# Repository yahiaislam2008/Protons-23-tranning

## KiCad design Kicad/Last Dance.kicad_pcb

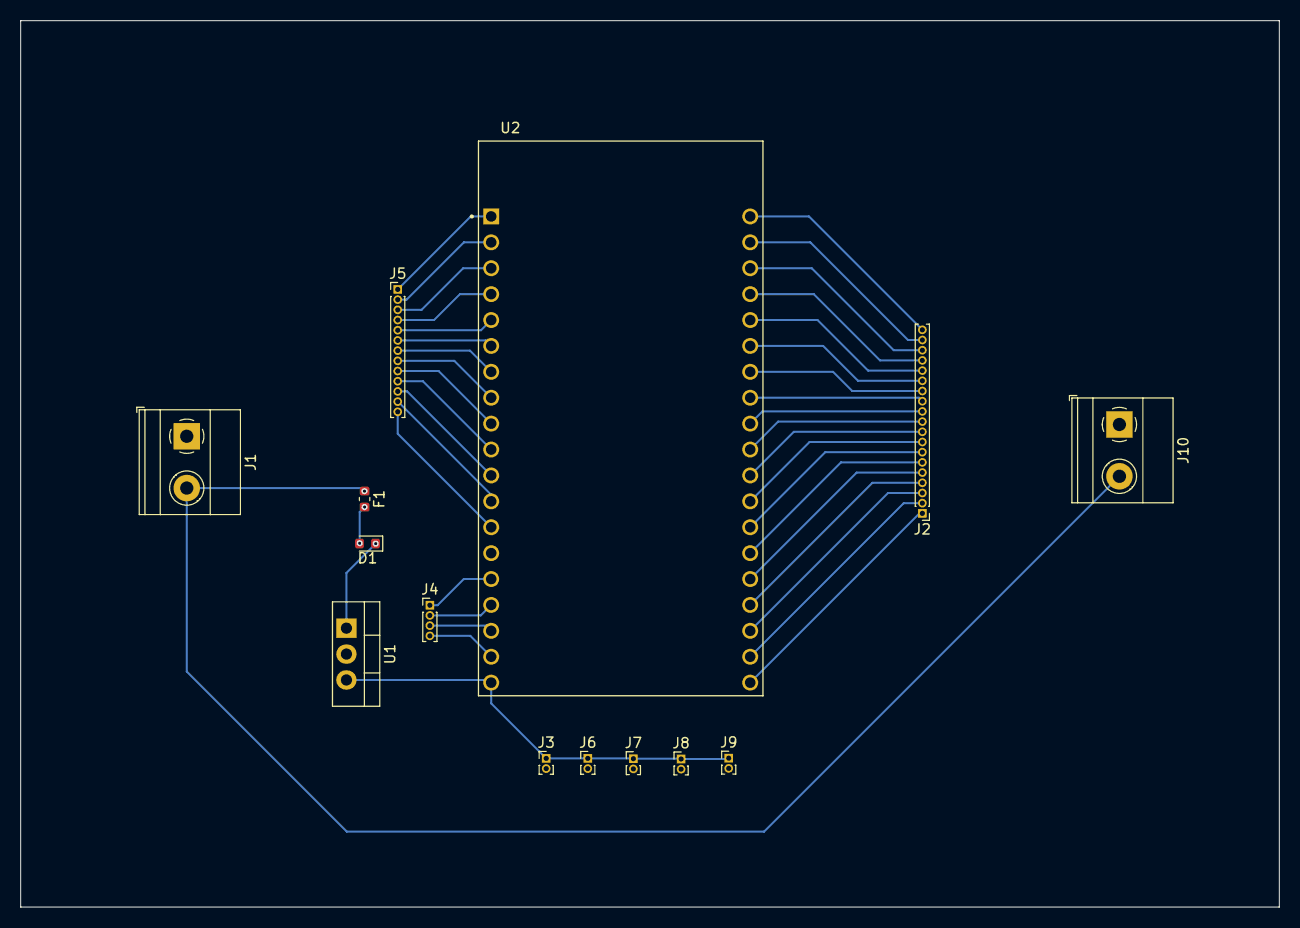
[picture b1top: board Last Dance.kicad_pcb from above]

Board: 2 copper layers, 123.4 x 86.9 mm, 14 parts (0 on the bottom side), 41 nets.

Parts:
D1: D; D_0603_1608Metric
F1: Fuse; Fuse_0603_1608Metric
J1, J10: Screw_Terminal_01x02; TerminalBlock_Phoenix_MKDS-1,5-2-5.08_1x02_P5.08mm_Horizont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
J2: Conn_01x19_Pin; PinHeader_1x19_P1.00mm_Vertical
J3, J6, J7, J8, J9: Conn_01x02_Pin; PinHeader_1x02_P1.00mm_Vertical
J4: Conn_01x04_Pin; PinHeader_1x04_P1.00mm_Vertical
J5: Conn_01x13_Pin; PinHeader_1x13_P1.00mm_Vertical
U1: LM7805_TO220; TO-220-3_Vertical
U2: ESP32-DEVKITC-32D; MODULE_ESP32-DEVKITC-32D

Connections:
+12V: F1.1, J1.2, J10.2
GND: J1.1, J3.2, J6.2, J7.2, J8.2, J9.2, J10.1, U1.2 (GND), U2.J2-14 (GND1)
unnamed: D1.2 (A), F1.2
unnamed: D1.1 (K), U1.1 (VI)
unnamed: J2.1, U2.J3-19 (CLK)
unnamed: J2.2, U2.J3-18 (SD0)
unnamed: J2.3, U2.J3-17 (SD1)
unnamed: J2.4, U2.J3-16 (IO15)
unnamed: J2.5, U2.J3-15 (IO2)
unnamed: J2.6, U2.J3-14 (IO0)
unnamed: J2.7, U2.J3-13 (IO4)
unnamed: J2.8, U2.J3-12 (IO16)
unnamed: J2.9, U2.J3-11 (IO17)
unnamed: J2.10, U2.J3-10 (IO5)
unnamed: J2.11, U2.J3-9 (IO18)
unnamed: J2.12, U2.J3-8 (IO19)
unnamed: J2.13, U2.J3-7 (GND2)
unnamed: J2.14, U2.J3-6 (IO21)
unnamed: J2.15, U2.J3-5 (RXD0)
unnamed: J2.16, U2.J3-4 (TXD0)
unnamed: J2.17, U2.J3-3 (IO22)
unnamed: J2.18, U2.J3-2 (IO23)
unnamed: J2.19, U2.J3-1 (GND3)
unnamed: J3.1, J6.1, J7.1, J8.1, J9.1, U1.3 (VO), U2.J2-19 (EXT_5V)
unnamed: J4.1, U2.J2-15 (IO13)
unnamed: J4.2, U2.J2-16 (SD2)
unnamed: J4.3, U2.J2-17 (SD3)
unnamed: J4.4, U2.J2-18 (CMD)
unnamed: J5.1, U2.J2-1 (3V3)
unnamed: J5.2, U2.J2-2 (EN)
unnamed: J5.3, U2.J2-3 (SENSOR_VP)
unnamed: J5.4, U2.J2-4 (SENSOR_VN)
unnamed: J5.5, U2.J2-5 (IO34)
unnamed: J5.6, U2.J2-6 (IO35)
unnamed: J5.7, U2.J2-7 (IO32)
unnamed: J5.8, U2.J2-8 (IO33)
unnamed: J5.9, U2.J2-9 (IO25)
unnamed: J5.10, U2.J2-10 (IO26)
unnamed: J5.11, U2.J2-11 (IO27)
unnamed: J5.12, U2.J2-12 (IO14)
unnamed: J5.13, U2.J2-13 (IO12)

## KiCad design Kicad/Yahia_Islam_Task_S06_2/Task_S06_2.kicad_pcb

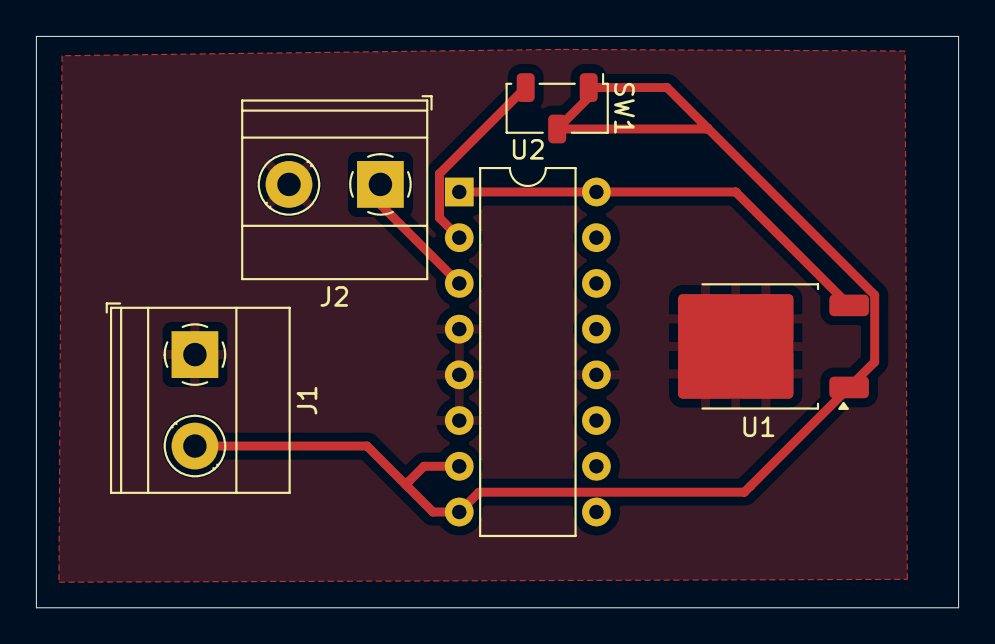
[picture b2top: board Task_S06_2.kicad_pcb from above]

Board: 2 copper layers, 51.2 x 31.7 mm, 5 parts (0 on the bottom side), 5 nets.

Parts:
J1, J2: Screw_Terminal_01x02; TerminalBlock_Phoenix_MKDS-1,5-2-5.08_1x02_P5.08mm_Horizont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
SW1: SW_SPDT_312; Nidec_Copal_CAS-120A
U1: L7805; TO-252-2
U2: L293D; DIP-16_W7.62mm

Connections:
+9V: J1.2, SW1.1 (B), SW1.2 (C), U1.1 (IN), U2.7 (2A), U2.8 (VCC2)
GND: J1.1, J2.2, U1.2 (GND), U2.4 (GND), U2.5 (GND), U2.6 (2Y), U2.12 (GND)
unnamed: J2.1, U2.3 (1Y)
unnamed: SW1.3 (A), U2.2 (1A)
unnamed: U1.3 (OUT), U2.1 (EN1,2), U2.16 (VCC1)

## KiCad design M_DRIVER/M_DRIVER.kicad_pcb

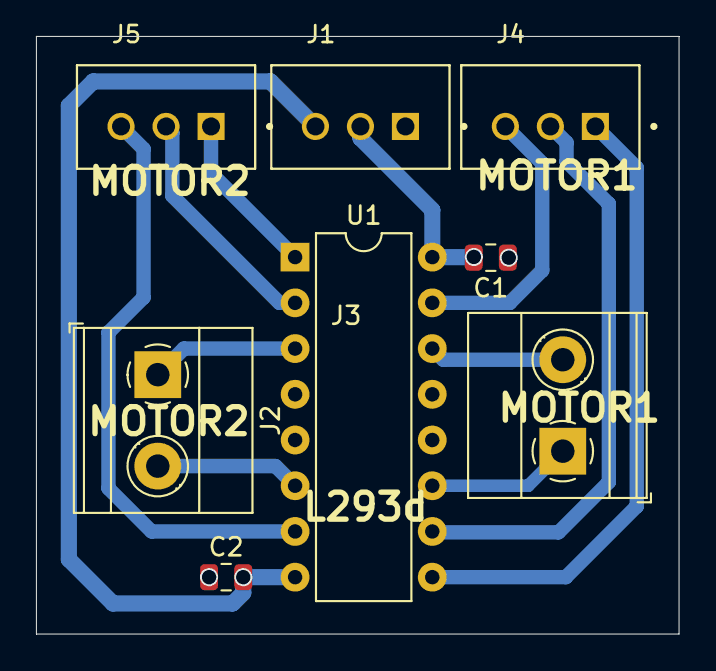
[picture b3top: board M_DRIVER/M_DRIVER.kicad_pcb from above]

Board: 2 copper layers, 35.7 x 33.2 mm, 8 parts (0 on the bottom side), 13 nets.

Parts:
C1, C2: 10 uF; C_0805_2012Metric
J1, J4, J5: B3B-XH-A_LF__SN_; JST_B3B-XH-A_LF__SN_
J2, J3: Screw_Terminal_01x02; TerminalBlock_Phoenix_MKDS-1,5-2-5.08_1x02_P5.08mm_Horizont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
U1: L293D; DIP-16_W7.62mm

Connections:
+5V: C1.2, J1.2, U1.16 (VCC1)
+12V: C2.2, J1.3, U1.8 (VCC2)
/M1: J4.2, U1.10 (3A)
/M2: J4.3, U1.15 (4A)
/M3: J5.2, U1.2 (1A)
/M4: J5.3, U1.7 (2A)
/PWM1: J4.1, U1.9 (EN3,4)
/PWM2: J5.1, U1.1 (EN1,2)
GND: C1.1, C2.1, J1.1, U1.4 (GND), U1.5 (GND), U1.12 (GND), U1.13 (GND)
unnamed: J2.1, U1.3 (1Y)
unnamed: J2.2, U1.6 (2Y)
unnamed: J3.1, U1.11 (3Y)
unnamed: J3.2, U1.14 (4Y)

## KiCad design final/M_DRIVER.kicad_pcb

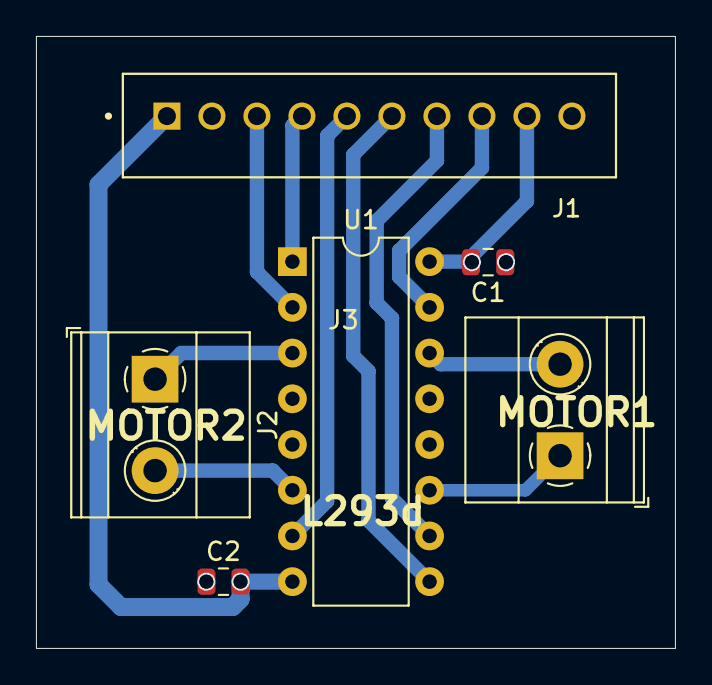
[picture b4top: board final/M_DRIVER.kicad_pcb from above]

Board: 2 copper layers, 35.5 x 34.0 mm, 6 parts (0 on the bottom side), 13 nets.

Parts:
C1, C2: 10 uF; C_0805_2012Metric
J1: B10B-XH-A_LF__SN_; JST_B10B-XH-A_LF__SN_
J2, J3: Screw_Terminal_01x02; TerminalBlock_Phoenix_MKDS-1,5-2-5.08_1x02_P5.08mm_Horizont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
U1: L293D; DIP-16_W7.62mm

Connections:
+5V: C1.2, J1.9, U1.16 (VCC1)
+12V: C2.2, J1.1, U1.8 (VCC2)
/M1: J1.7, U1.10 (3A)
/M2: J1.8, U1.15 (4A)
/M3: J1.3, U1.2 (1A)
/M4: J1.5, U1.7 (2A)
/PWM1: J1.6, U1.9 (EN3,4)
/PWM2: J1.4, U1.1 (EN1,2)
GND: C1.1, C2.1, J1.2, J1.10, U1.4 (GND), U1.5 (GND), U1.12 (GND), U1.13 (GND)
unnamed: J2.1, U1.3 (1Y)
unnamed: J2.2, U1.6 (2Y)
unnamed: J3.1, U1.11 (3Y)
unnamed: J3.2, U1.14 (4Y)
